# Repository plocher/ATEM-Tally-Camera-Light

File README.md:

# ATEM-Tally-Camera-Light
## License: MIT License

Part 2 of a RFM69-based BlackMagic ATEM Tally Light system - On Camera Light

Part 1 is the SDI-connected controller
Part 2 is the on-camera tally light display

The controller uses the BMD SDI-Shield as an I2C interface to the control signals embedded in the SDI video stream emitted by the ATEM switchers, connected to an AdaFruit RadioFeather AVR 32u4 RFM69 controller and an AdaFruit neopixel strip.  

The Tally light receivers use the same AdaFruit RadioFeather RFM68 AVR 32U4 sticks with a NeoPixel strip that displays Red (LIVE), Green (PREVIEW) or dim Blue (operational, but not currently selected).

The Arduino IDE sketch is available on GitHub (... TBD URL ...)

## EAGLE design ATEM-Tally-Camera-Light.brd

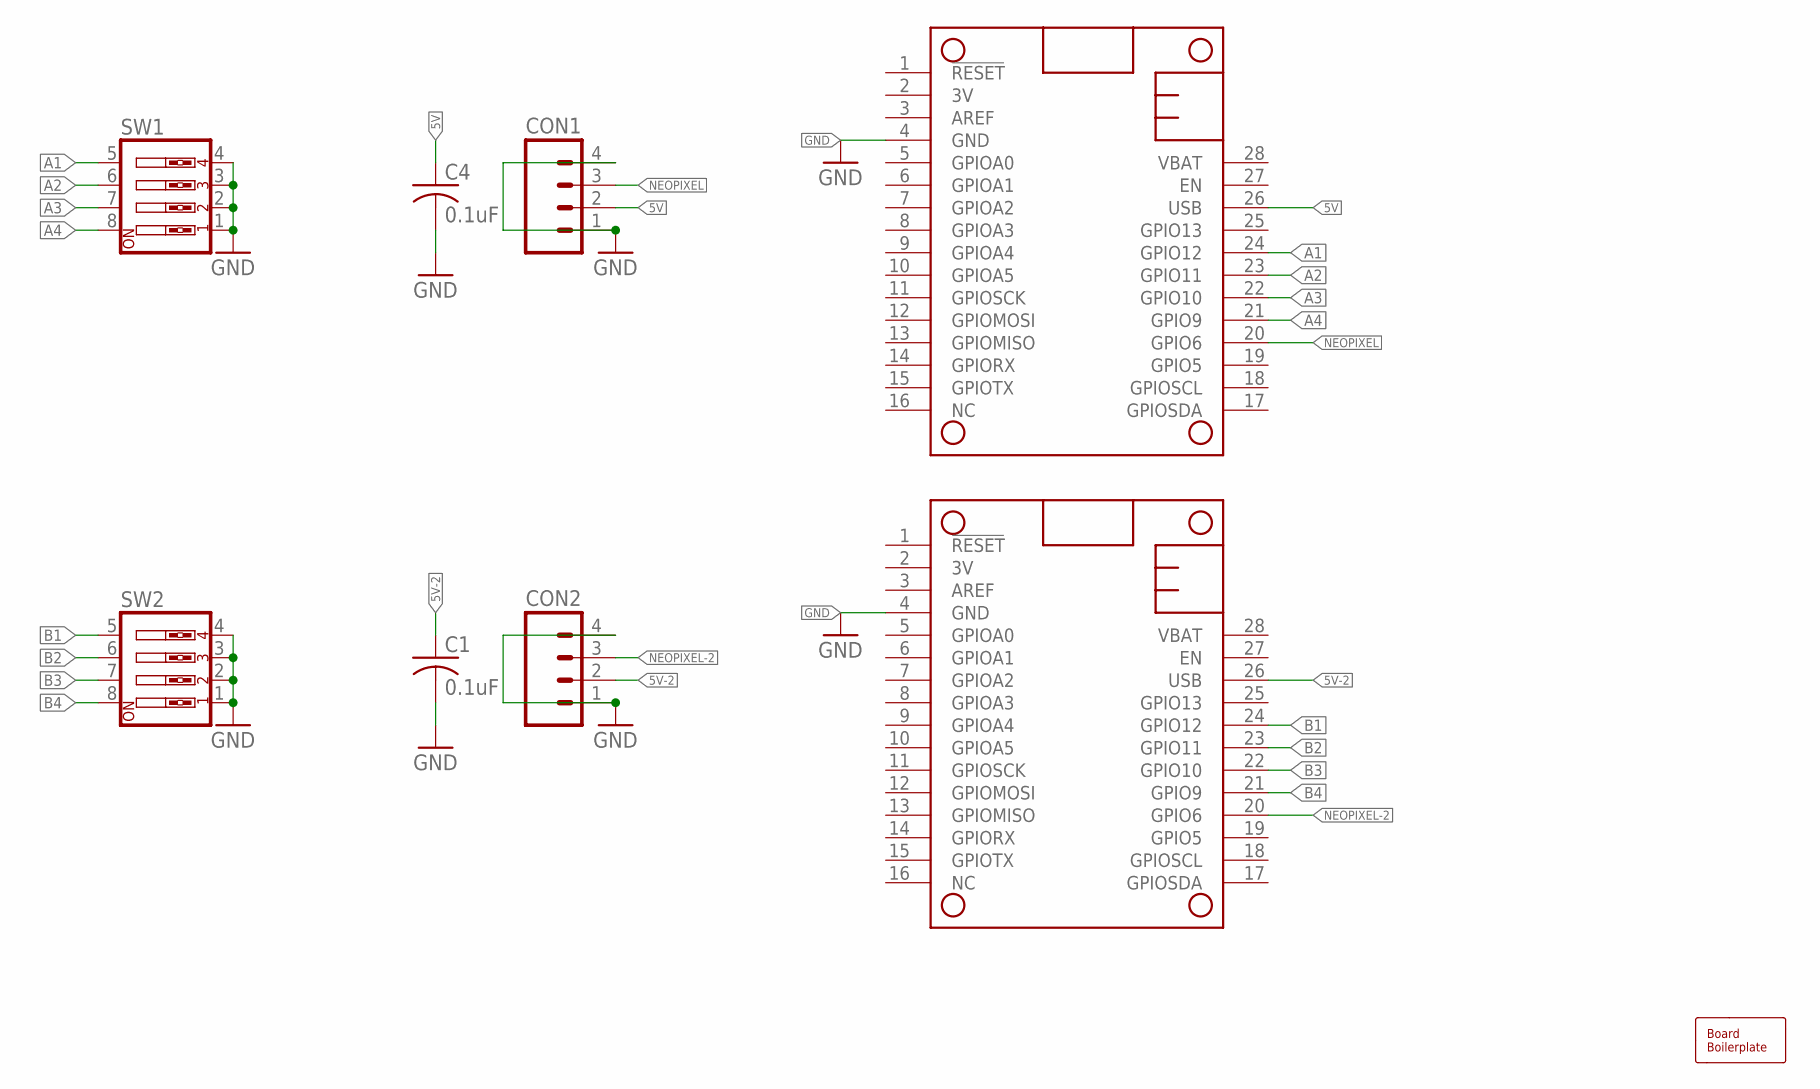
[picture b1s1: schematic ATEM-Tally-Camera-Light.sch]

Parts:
BOARD1: BOARD80X50; BOARD-DINRAIL-3.17INX5CM
C1, C4: 0.1uF; 0603-CAP
CON1, CON2: CONNECTOR-M04LOCK; 1X04_LOCK
MS1, MS2: FEATHERWING_NODIM; FEATHERWING_DIM
SW1, SW2: SW_DIP-4; EDG-04

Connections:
5V: C4.1, CON1.2, MS1.26 (USB)
5V-2: C1.1, CON2.2, MS2.26 (USB)
A1: MS1.24 (GPIO12), SW1.5
A2: MS1.23 (GPIO11), SW1.6
A3: MS1.22 (GPIO10), SW1.7
A4: MS1.21 (GPIO9), SW1.8
B1: MS2.24 (GPIO12), SW2.5
B2: MS2.23 (GPIO11), SW2.6
B3: MS2.22 (GPIO10), SW2.7
B4: MS2.21 (GPIO9), SW2.8
GND: C1.2, C4.2, CON1.1, CON1.4, CON2.1, CON2.4, MS1.4 (GND), MS2.4 (GND), SW1.1, SW1.2, SW1.3, SW1.4, SW2.1, SW2.2, SW2.3, SW2.4
NEOPIXEL: CON1.3, MS1.20 (GPIO6)
NEOPIXEL-2: CON2.3, MS2.20 (GPIO6)

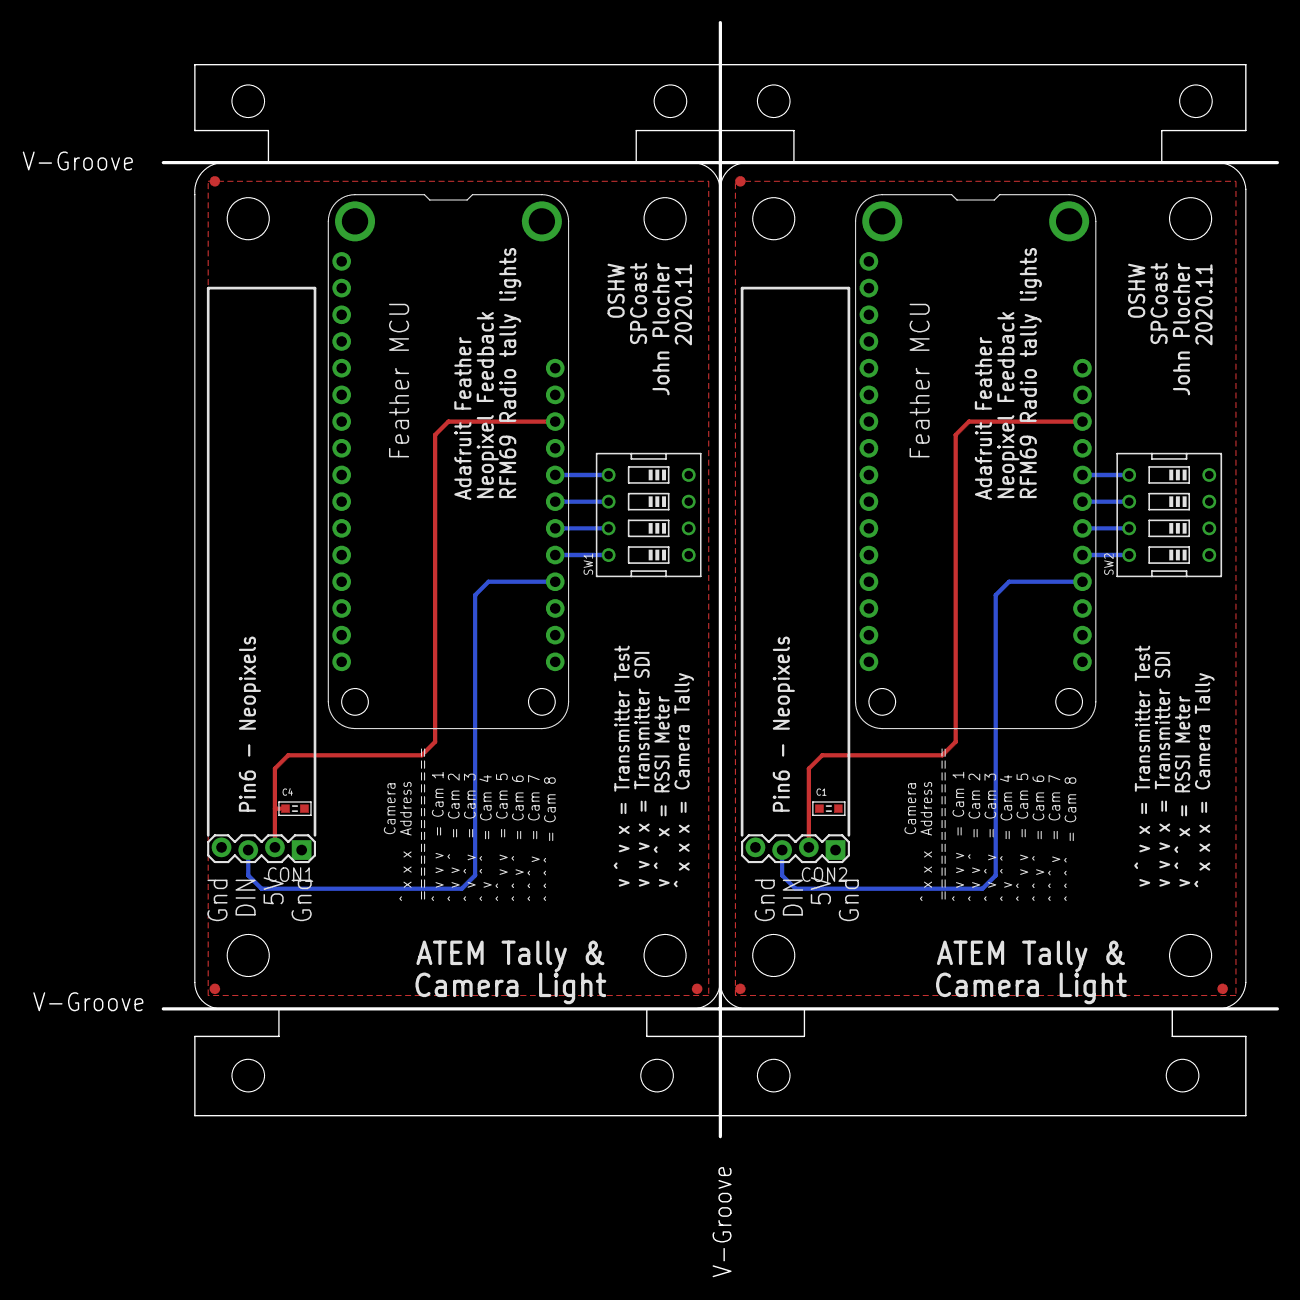
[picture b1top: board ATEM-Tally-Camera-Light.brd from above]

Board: 2 copper layers, 106.0 x 106.0 mm, 9 parts (0 on the bottom side), 13 nets.

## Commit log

2020-10-27 Initial version
2020-12-13 assembly pix
2020-12-13 build notes
2020-12-13 bugfix
